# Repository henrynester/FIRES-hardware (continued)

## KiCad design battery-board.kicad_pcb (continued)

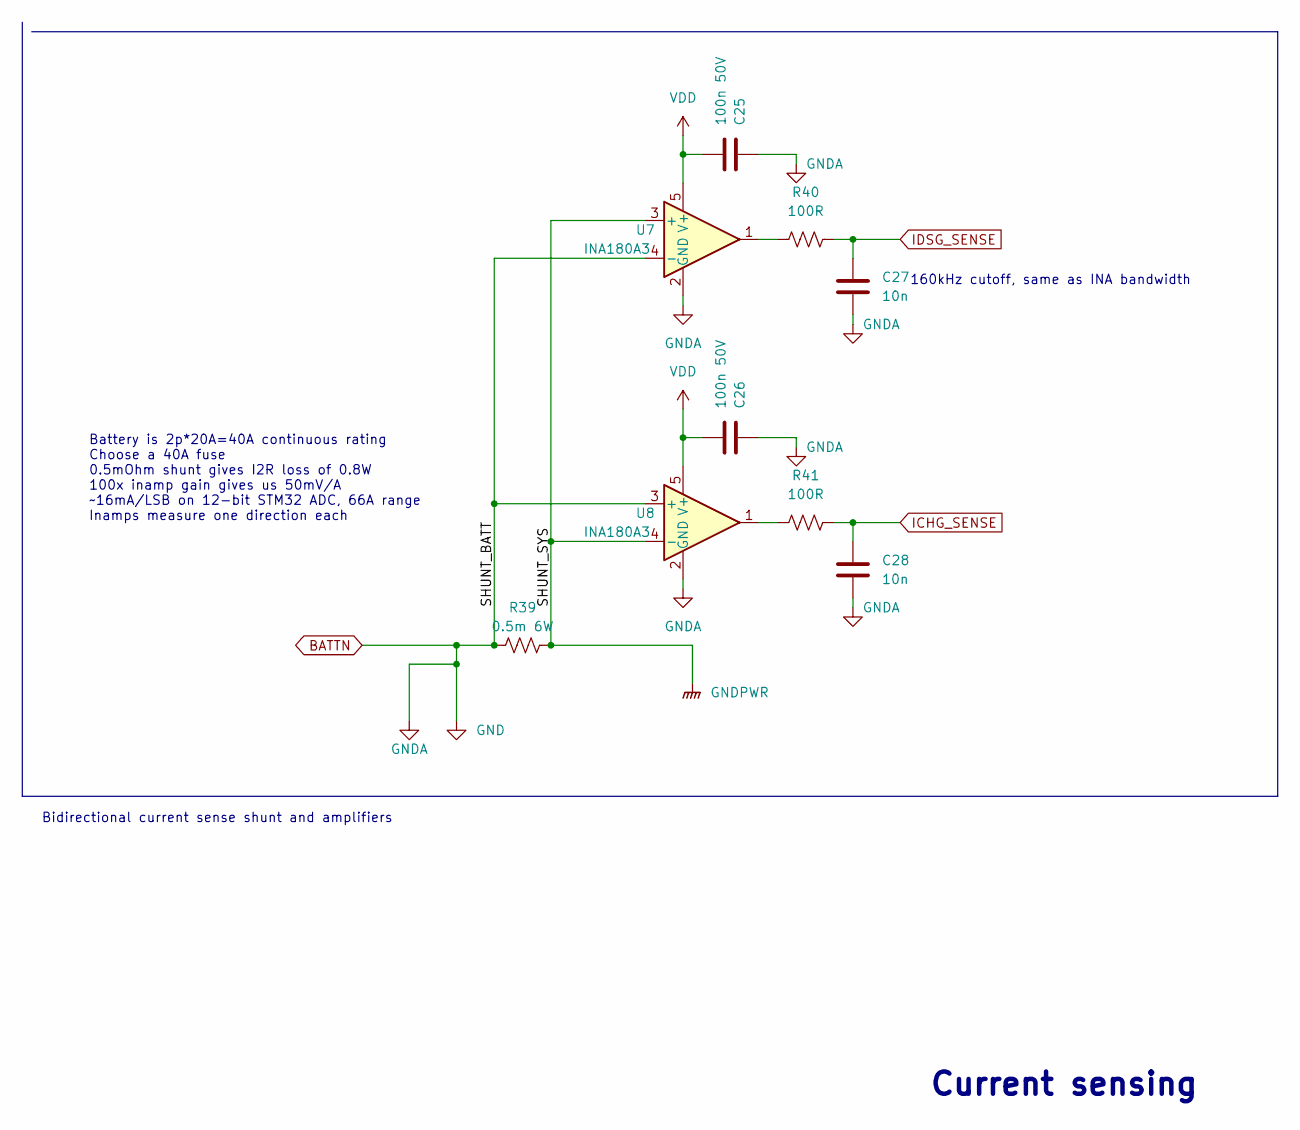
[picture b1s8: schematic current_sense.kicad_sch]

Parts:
C25, C26: 100n 50V; C_0805_2012Metric; part_number GCD21BR71H104KA01L
C27, C28: 10n; R_0805_2012Metric_Pad1.20x1.40mm_HandSolder; part_number GCM219R71H103KA37D
R39: 0.5m 6W; R_2512_6332Metric; part_number SSA2512L0M50FWR
R40, R41: 100R; R_0805_2012Metric_Pad1.20x1.40mm_HandSolder; part_number RC0805FR-07100RL
U7, U8: INA180A3; SOT-23-5; part_number INA180A3

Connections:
BATTN: C25.1, C26.1, C27.2, C28.2, R39.2, U7.2 (GND), U7.4 (-), U8.2 (GND), U8.3 (+); also elsewhere on the board
GNDPWR: R39.1, U7.3 (+), U8.4 (-); also elsewhere on the board
ICHG_SENSE: C28.1, R41.1; also elsewhere on the board
IDSG_SENSE: C27.1, R40.1; also elsewhere on the board
unnamed: R40.2, U7.1
unnamed: R41.2, U8.1
VDD: C25.2, C26.2, U7.5 (V+), U8.5 (V+); also elsewhere on the board

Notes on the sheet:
160kHz cutoff, same as INA bandwidth
Battery is 2p*20A=40A continuous rating Choose a 40A fuse 0.5mOhm shunt gives I2R loss of 0.8W 100x inamp gain gives us 50mV/A ~16mA/LSB on 12-bit STM32 ADC, 66A range Inamps measure one direction each
Current sensing
Bidirectional current sense shunt and amplifiers

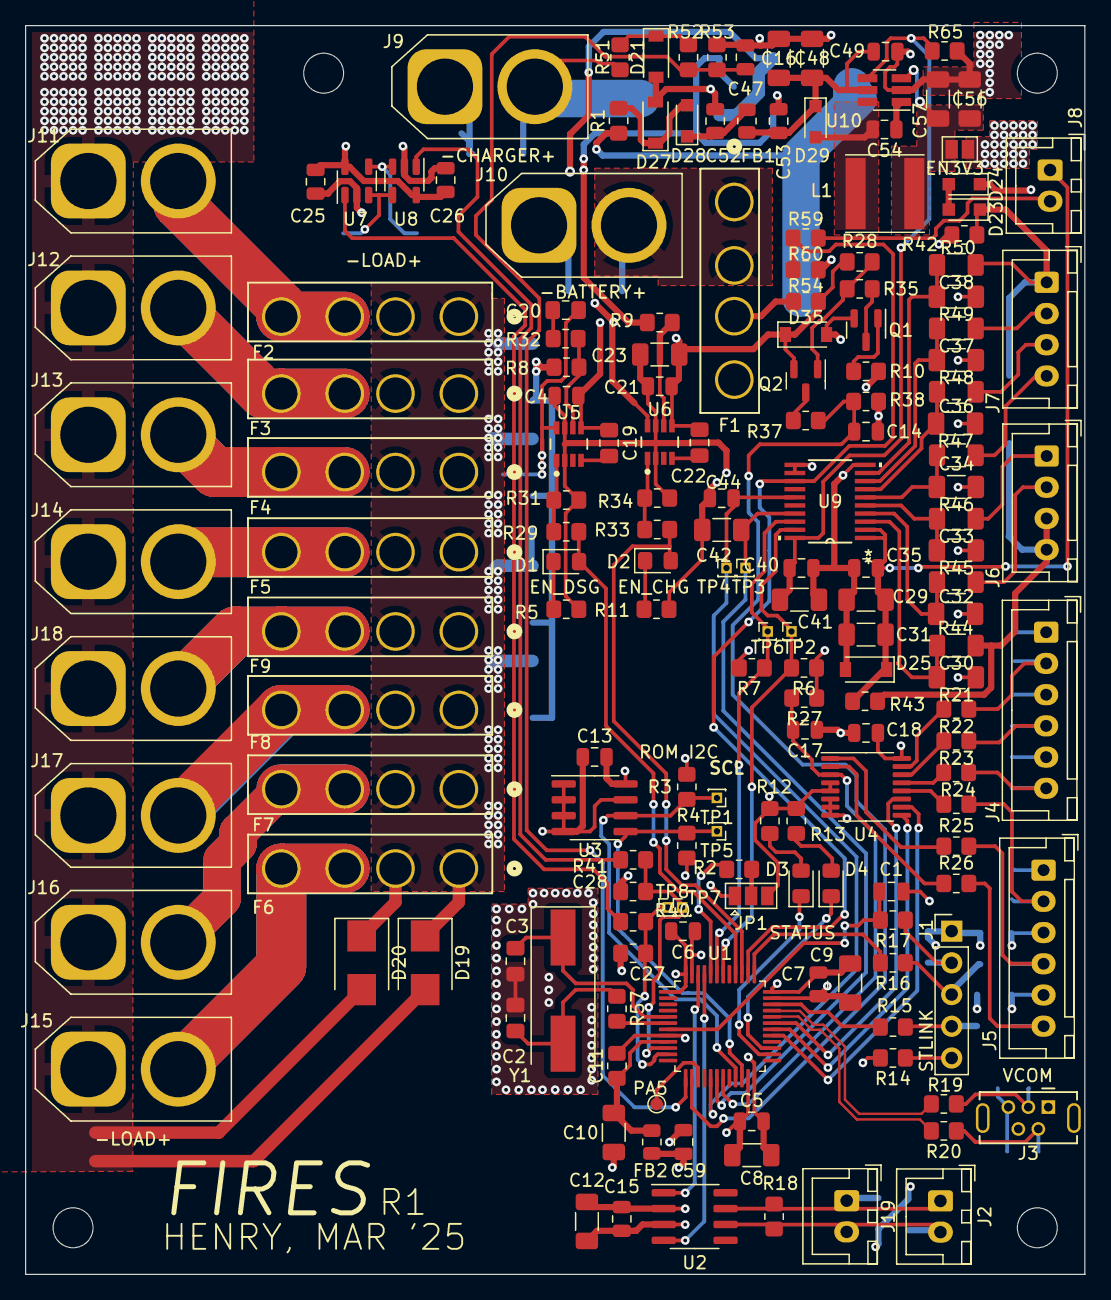
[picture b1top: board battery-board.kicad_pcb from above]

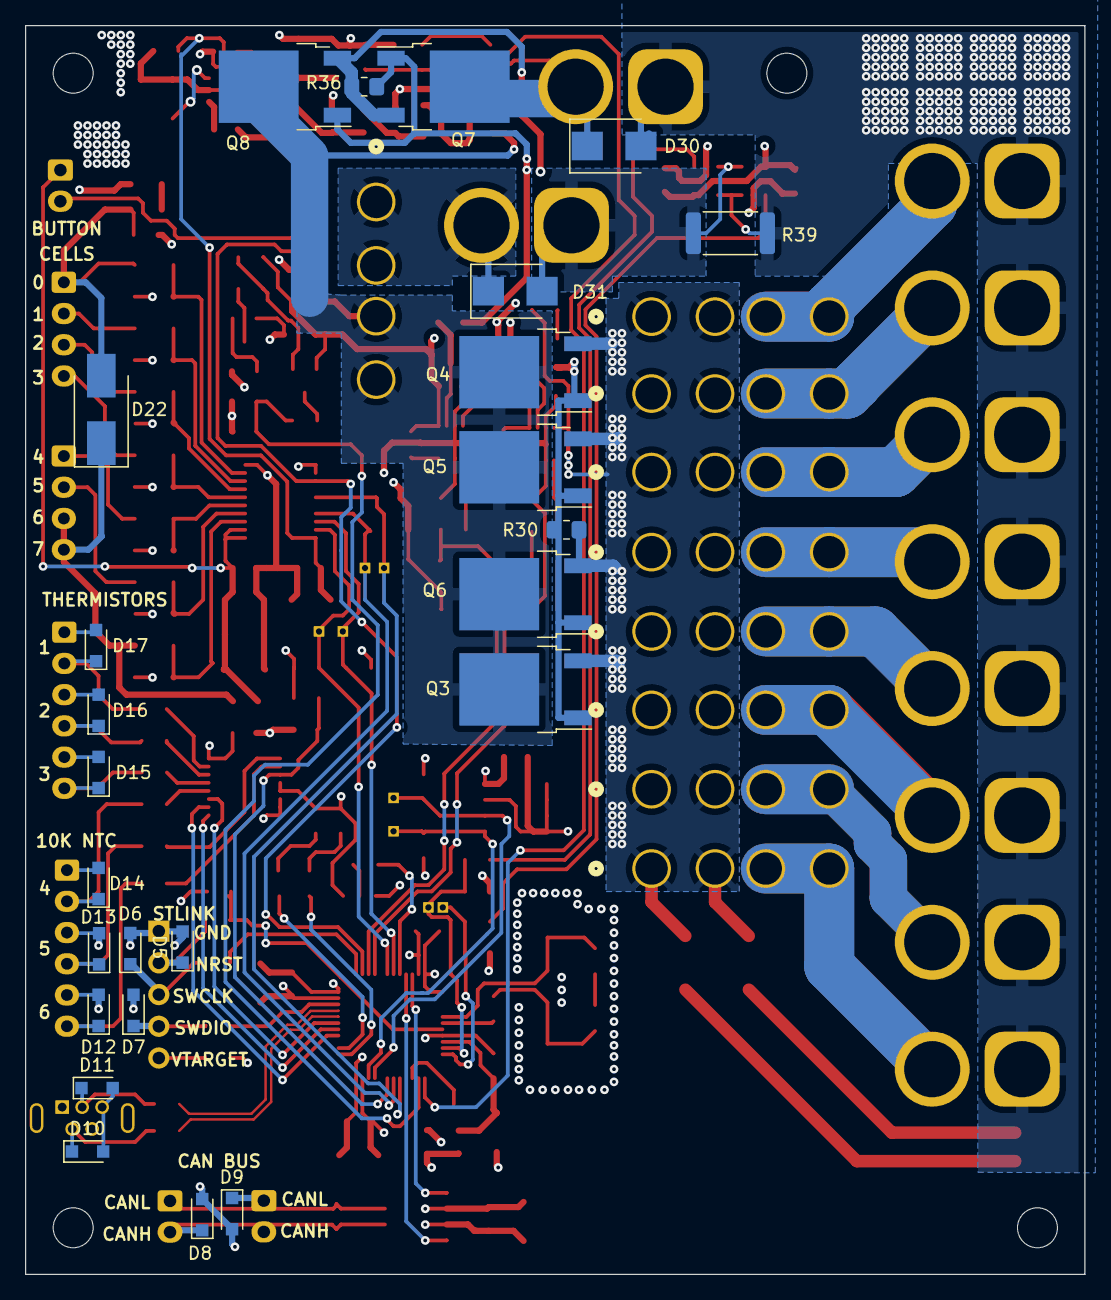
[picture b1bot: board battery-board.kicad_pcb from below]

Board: 4 copper layers, 84.8 x 100.0 mm, 203 parts (25 on the bottom side), 114 nets.

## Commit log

2025-03-19 removed stupid
2025-03-20 gerber output
2025-03-20 add sch
